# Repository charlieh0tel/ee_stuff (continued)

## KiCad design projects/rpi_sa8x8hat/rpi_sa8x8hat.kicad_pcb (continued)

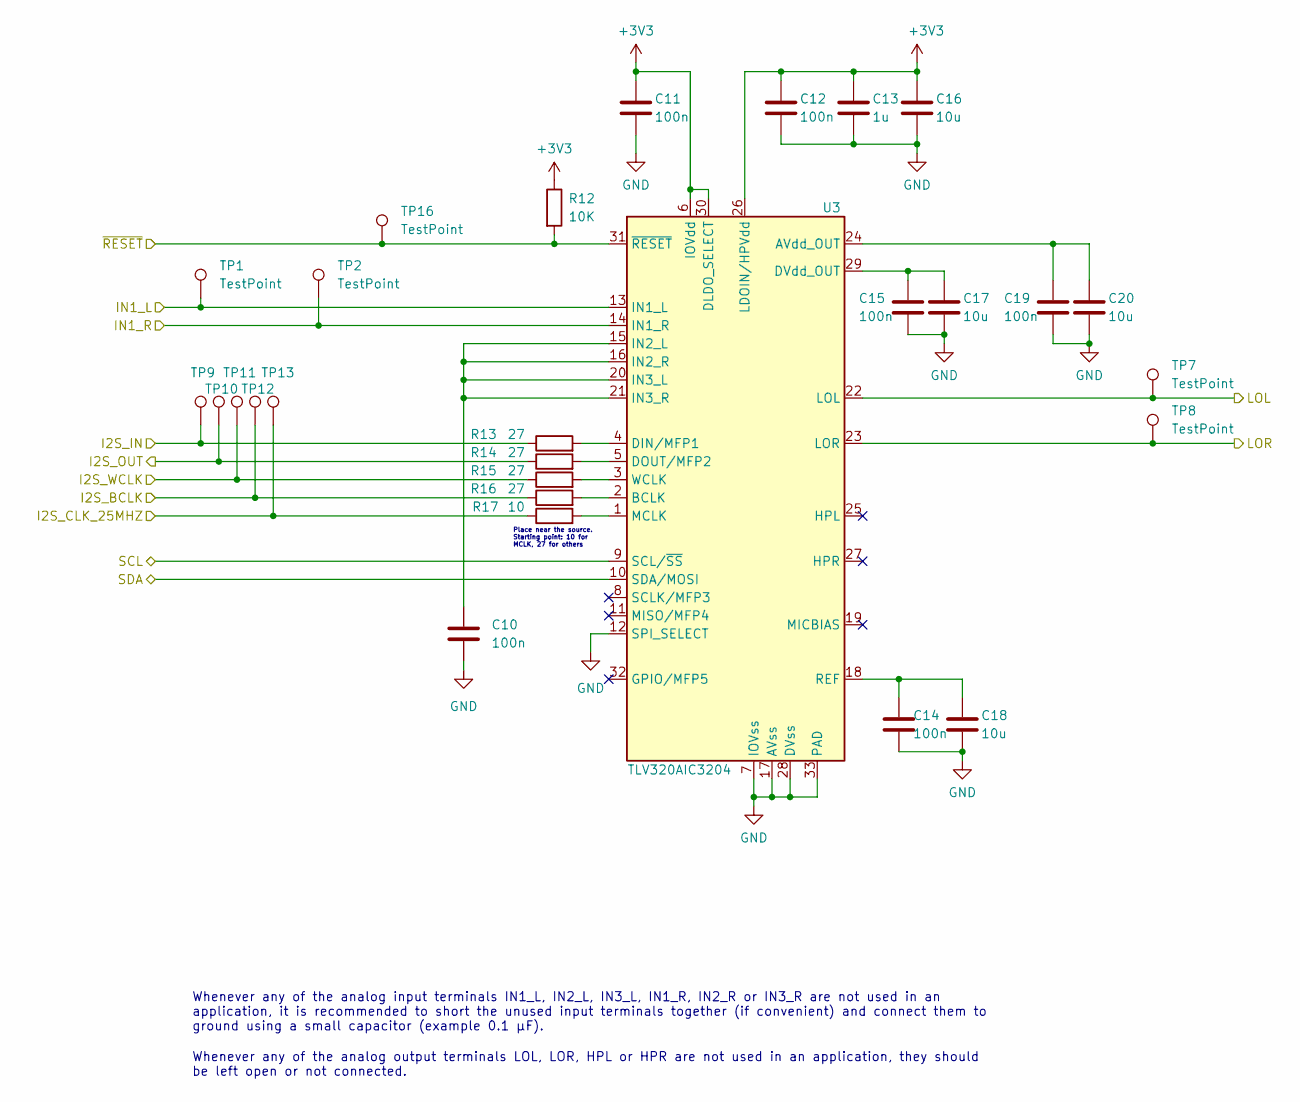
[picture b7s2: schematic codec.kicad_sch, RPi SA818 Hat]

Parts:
C10, C11, C12, C14, C15, C19: 100n; C_0402_1005Metric
C13: 1u; C_0402_1005Metric
C16, C17, C18, C20: 10u; C_0402_1005Metric
R12: 10K; R_0201_0603Metric
R13, R14, R15, R16: 27; R_0201_0603Metric
R17: 10; R_0201_0603Metric
TP1, TP2, TP7, TP8, TP9, TP10, TP11, TP12, TP13, TP16: TestPoint; TestPoint_Pad_D1.0mm
U3: TLV320AIC3204; QFN-32-1EP_5x5mm_P0.5mm_EP3.7x3.7mm

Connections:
+3V3: C11.1, C12.1, C13.1, C16.1, R12.1, U3.6 (IOVdd), U3.26 (LDOIN/HPVdd), U3.30 (DLDO_SELECT); also elsewhere on the board
/BCM_CLK_25MHZ: R17.1, TP13.1; also elsewhere on the board
/BCM_GPIO13: R12.2, TP16.1, U3.31 (~RESET); also elsewhere on the board
/BCM_I2S_BCLK: R16.1, TP12.1; also elsewhere on the board
/BCM_I2S_IN: R14.1, TP10.1; also elsewhere on the board
/BCM_I2S_OUT: R13.1, TP9.1; also elsewhere on the board
/BCM_I2S_WCLK: R15.1, TP11.1; also elsewhere on the board
/BCM_SCL: U3.9 (SCL/~SS); also elsewhere on the board
/BCM_SDA: U3.10 (SDA/MOSI); also elsewhere on the board
/Codec/IN1_L: TP1.1, U3.13 (IN1_L); also elsewhere on the board
/Codec/IN1_R: TP2.1, U3.14 (IN1_R); also elsewhere on the board
/Codec/LOL: TP7.1, U3.22 (LOL); also elsewhere on the board
/Codec/LOR: TP8.1, U3.23 (LOR); also elsewhere on the board
GND: C10.2, C11.2, C12.2, C13.2, C14.2, C15.2, C16.2, C17.2, C18.2, C19.2, C20.2, U3.7 (IOVss), U3.12 (SPI_SELECT), U3.17 (AVss), U3.28 (DVss), U3.33 (PAD); also elsewhere on the board
unnamed: C19.1, C20.1, U3.24 (AVdd_OUT)
unnamed: R16.2, U3.2 (BCLK)
unnamed: R13.2, U3.4 (DIN/MFP1)
unnamed: R14.2, U3.5 (DOUT/MFP2)
unnamed: C15.1, C17.1, U3.29 (DVdd_OUT)
unnamed: C10.1, U3.15 (IN2_L), U3.16 (IN2_R), U3.20 (IN3_L), U3.21 (IN3_R)
unnamed: R17.2, U3.1 (MCLK)
unnamed: C14.1, C18.1, U3.18 (REF)
unnamed: R15.2, U3.3 (WCLK)

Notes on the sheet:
Whenever any of the analog input terminals IN1_L, IN2_L, IN3_L, IN1_R, IN2_R or IN3_R are not used in an application, it is recommended to short the unused input terminals together (if convenient) and connect them to ground using a small capacitor (example 0.1 µF).
Place near the source. Starting point: 10 for MCLK, 27 for others
Whenever any of the analog output terminals LOL, LOR, HPL or HPR are not used in an application, they should be left open or not connected.

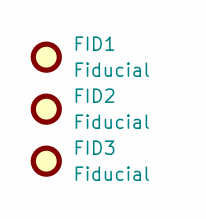
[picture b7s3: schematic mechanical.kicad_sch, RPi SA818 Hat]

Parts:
FID1, FID2, FID3: Fiducial; Fiducial_0.5mm_Mask1mm

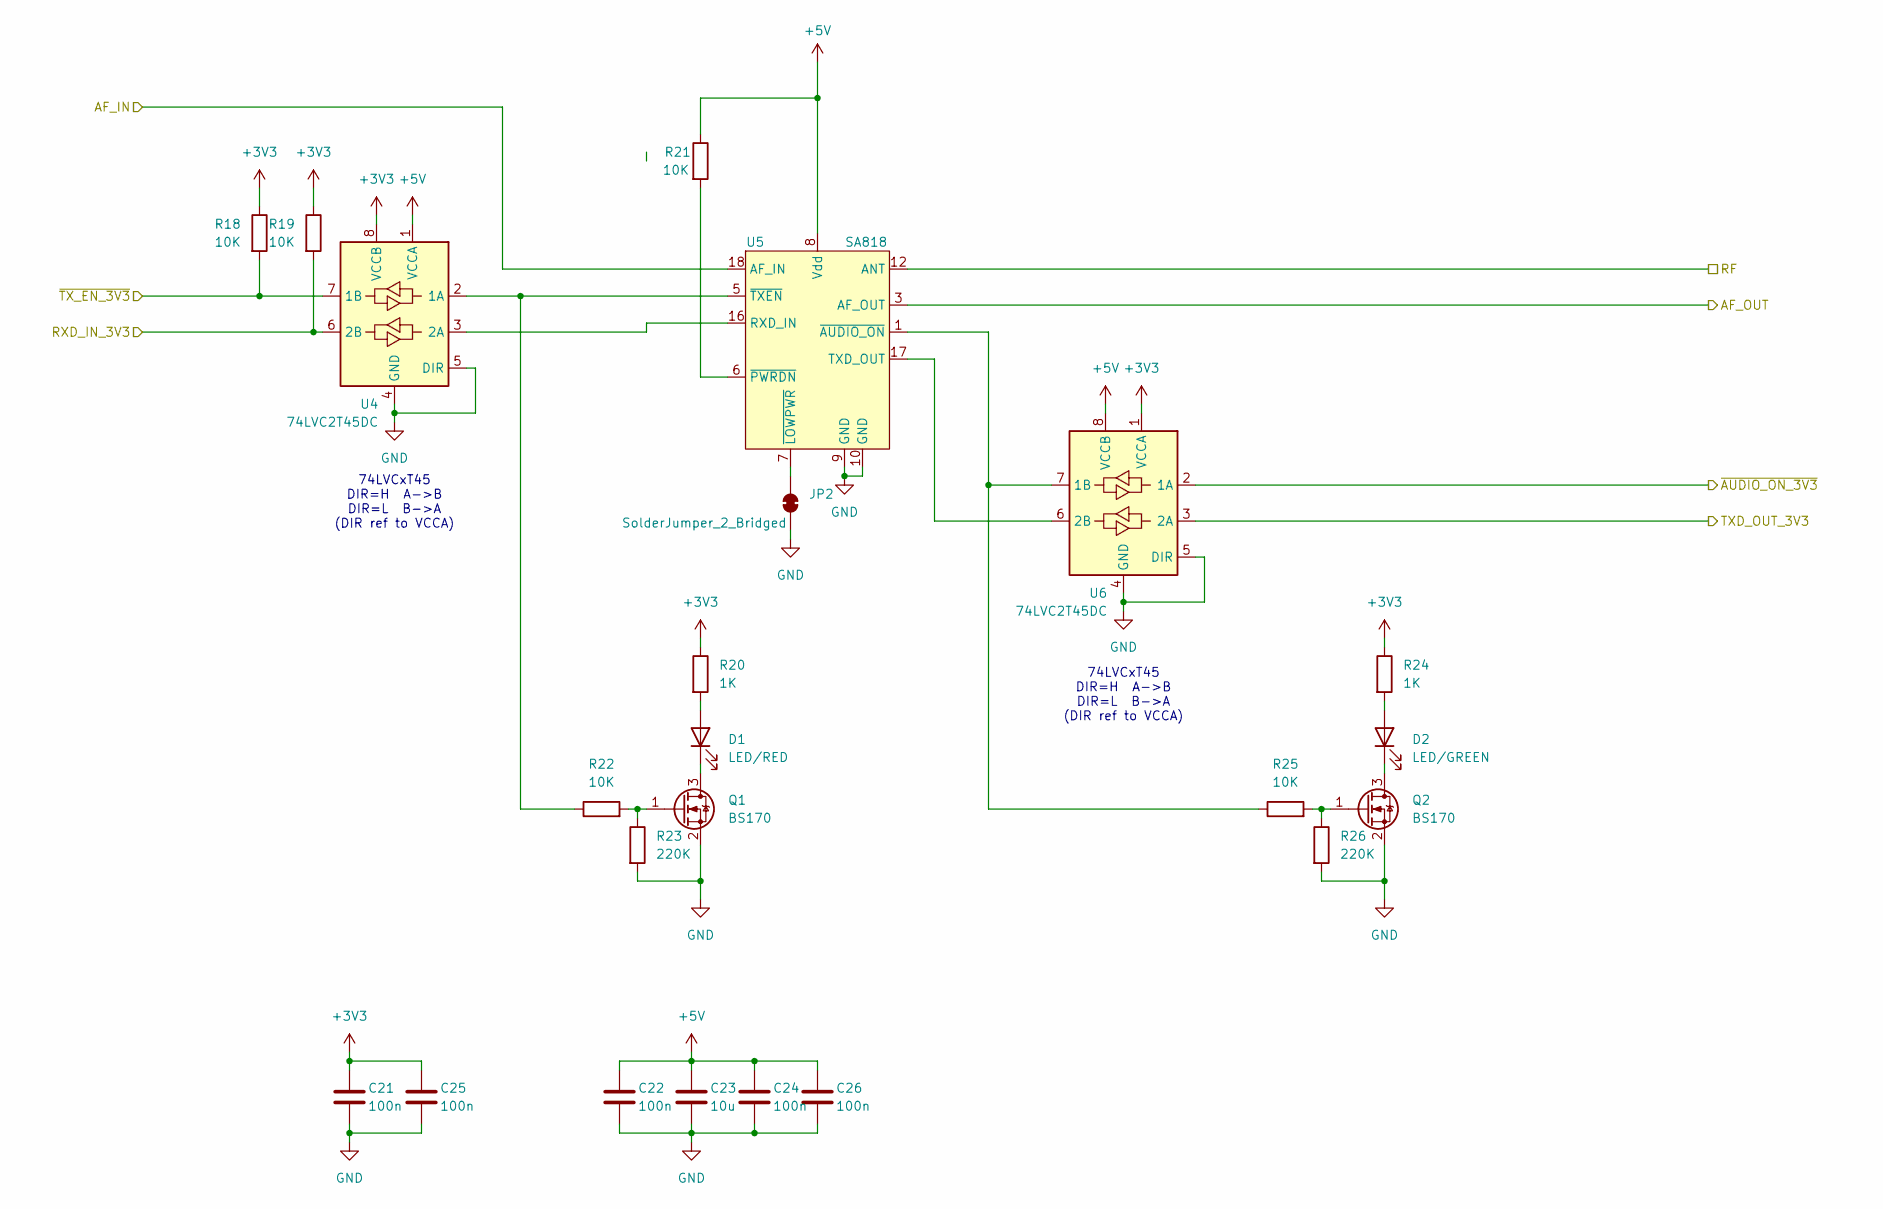
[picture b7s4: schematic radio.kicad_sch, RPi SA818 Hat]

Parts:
C21, C22, C24, C25, C26: 100n; C_0402_1005Metric
C23: 10u; C_0402_1005Metric
D1: LED/RED; LED_0603_1608Metric
D2: LED/GREEN; LED_0603_1608Metric
JP2: SolderJumper_2_Bridged; SolderJumper-2_P1.3mm_Bridged2Bar_Pad1.0x1.5mm
Q1, Q2: BS170; SOT-23
R18, R19, R21, R22, R25: 10K; R_0201_0603Metric
R20, R24: 1K; R_0402_1005Metric
R23, R26: 220K; R_0201_0603Metric
U4, U6: 74LVC2T45DC; VSSOP-8_2.3x2mm_P0.5mm
U5: SA818; SA8x8

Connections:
+3V3: C21.1, C25.1, R18.1, R19.1, R20.1, R24.1, U4.8 (VCCB), U6.1 (VCCA); also elsewhere on the board
+5V: C22.1, C23.1, C24.1, C26.1, R21.1, U4.1 (VCCA), U5.8 (Vdd), U6.8 (VCCB); also elsewhere on the board
/BCM12_GPIO: R18.2, U4.7 (1B); also elsewhere on the board
/BCM25_GPIO: U6.2 (1A); also elsewhere on the board
/BCM_RXD_IN: U6.3 (2A); also elsewhere on the board
/BCM_TXD_OUT: R19.2, U4.6 (2B); also elsewhere on the board
/L_IN: U5.3 (AF_OUT); also elsewhere on the board
/L_OUT: U5.18 (AF_IN); also elsewhere on the board
/Radio/RF: U5.12 (ANT); also elsewhere on the board
GND: C21.2, C22.2, C23.2, C24.2, C25.2, C26.2, JP2.1 (A), Q1.2 (S), Q2.2 (S), R23.2, R26.2, U4.4 (GND), U4.5 (DIR), U5.9 (GND), U5.10 (GND), U6.4 (GND), U6.5 (DIR); also elsewhere on the board
unnamed: D1.2 (A), R20.2
unnamed: D1.1 (K), Q1.3 (D)
unnamed: D2.2 (A), R24.2
unnamed: D2.1 (K), Q2.3 (D)
unnamed: JP2.2 (B), U5.7 (~LOWPWR)
unnamed: Q1.1 (G), R22.2, R23.1
unnamed: Q2.1 (G), R25.2, R26.1
unnamed: R22.1, U4.2 (1A), U5.5 (~TXEN)
unnamed: U4.3 (2A), U5.16 (RXD_IN)
unnamed: U5.17 (TXD_OUT), U6.6 (2B)
unnamed: R25.1, U5.1 (~AUDIO_ON), U6.7 (1B)
unnamed: R21.2, U5.6 (~PWRDN)

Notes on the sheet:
74LVCxT45 DIR=H A->B DIR=L B->A (DIR ref to VCCA)

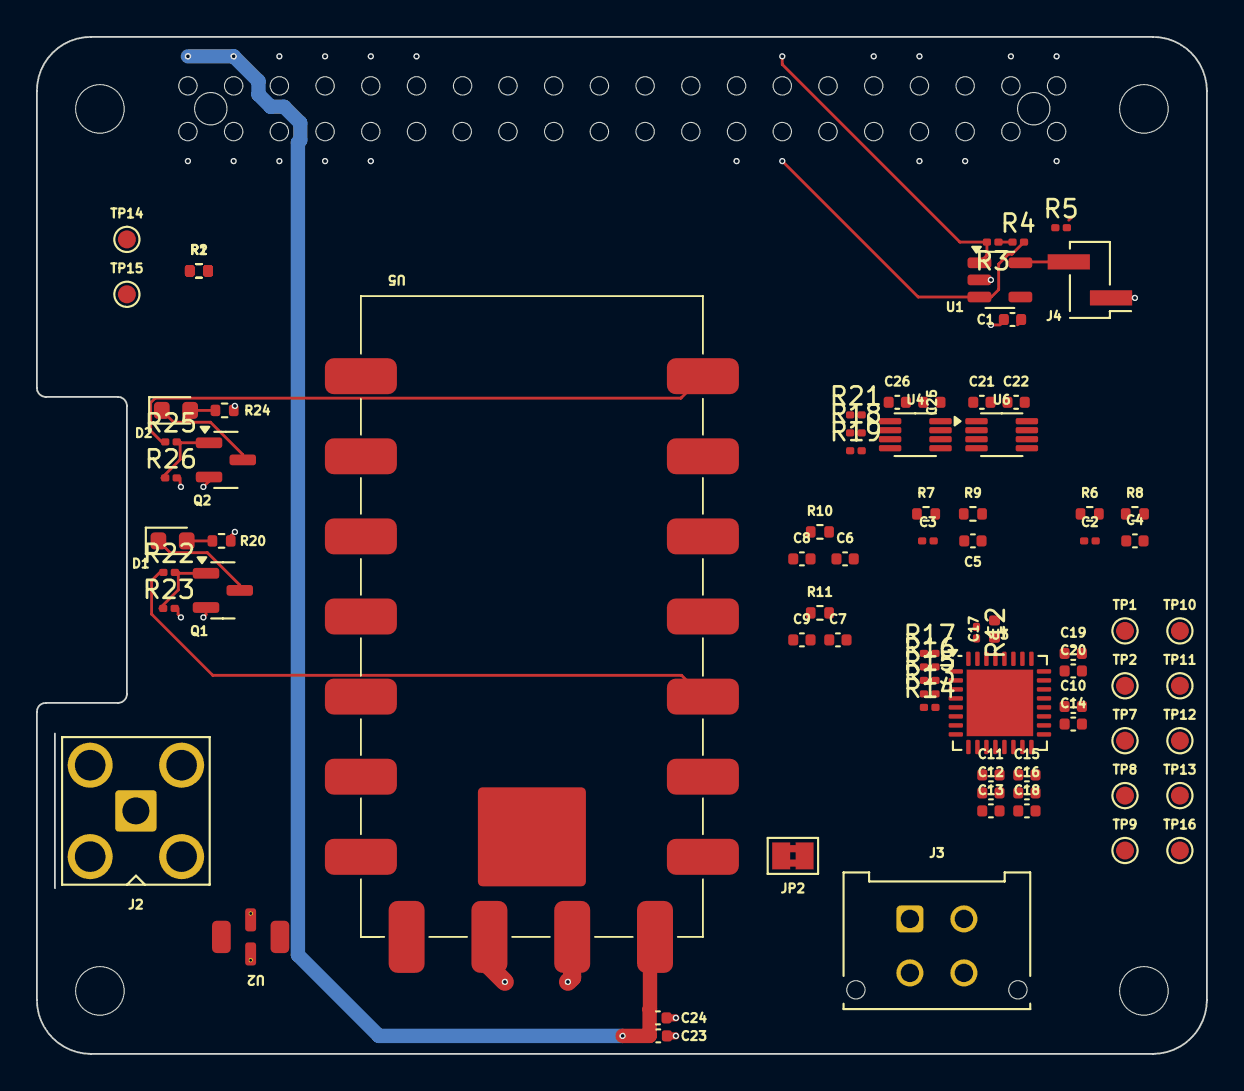
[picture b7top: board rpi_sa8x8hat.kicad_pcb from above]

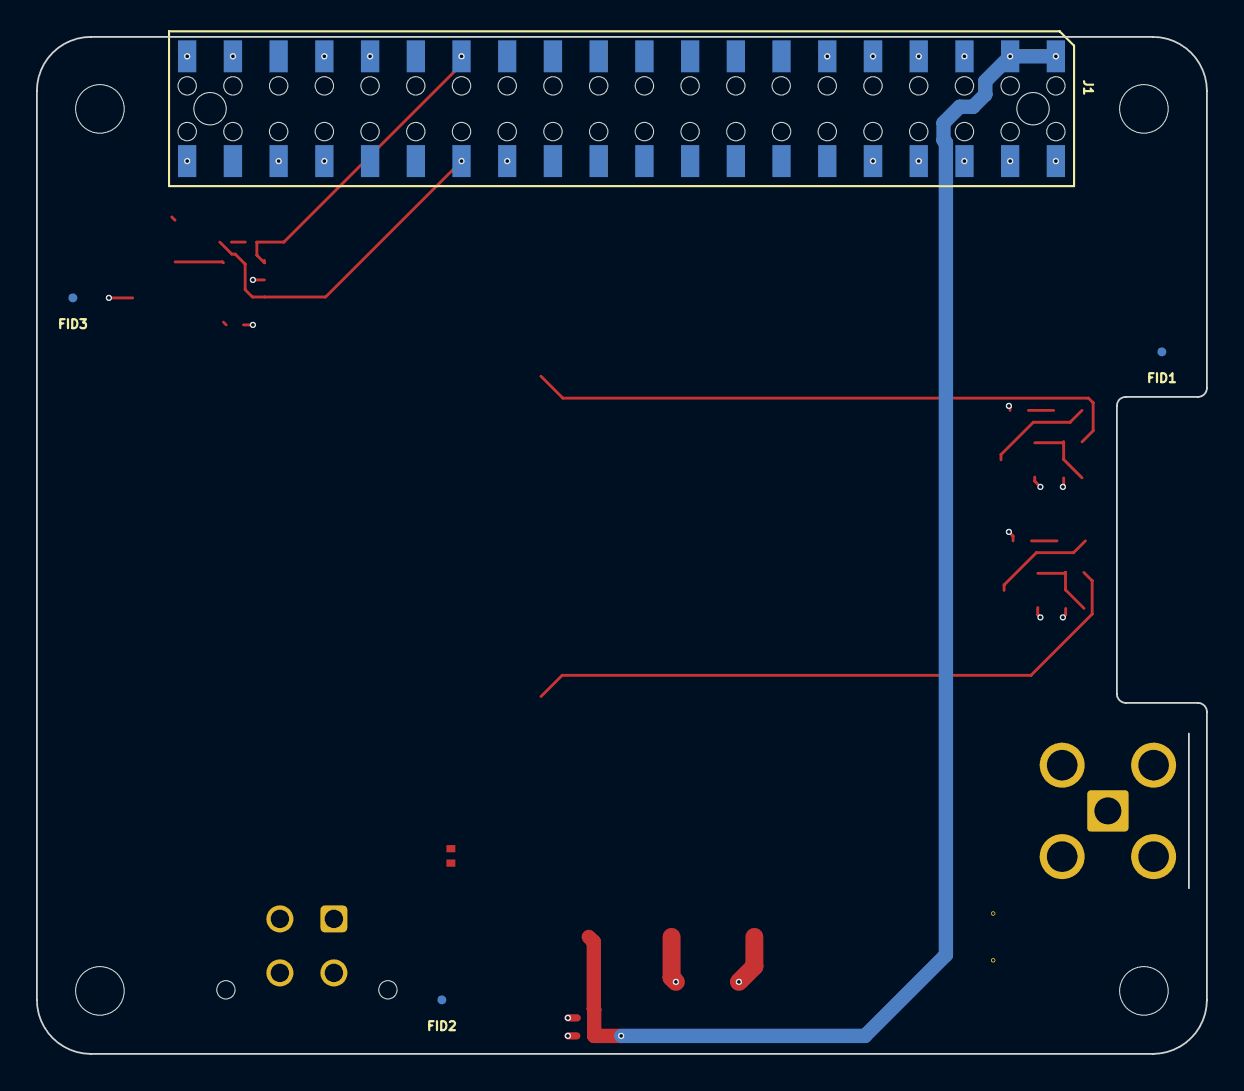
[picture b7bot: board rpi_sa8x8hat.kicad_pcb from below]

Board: 4 copper layers, 65.0 x 56.5 mm, 86 parts (4 on the bottom side), 53 nets.

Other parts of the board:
MH1, MH2, MH3, MH4: MountingHole_2.7mm_M2.5

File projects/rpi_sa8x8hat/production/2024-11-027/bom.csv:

Designator,Footprint,Quantity,Value,LCSC Part #
"C1, C10, C11, C12, C14, C15, C19, C21, C22, C24, C25, C26",0402,12,100n,
C13,0402,1,1u,
"C16, C17, C18, C20, C23",0402,5,10u,
"C2, C3",0201,2,2.2u,
"C4, C5",0402,2,33p,
"C6, C7",0402,2,4.7n,
"C8, C9",0402,2,2.2u,
D1,0603,1,LED/RED,
D2,0603,1,LED/GREEN,
"FID1, FID2, FID3",Fiducial_0.5mm_Mask1mm,3,Fiducial,
"H1, H2, H3, H4",RPi_Hat_Mounting_Hole,4,MountingHole_Pad,
J1,Samtec_HLE-120-02-XXX-DV-BE-XX-XX,1,RPi_GPIO,
J2,SMA_Amphenol_901-143_Horizontal,1,Conn_Coaxial_Small,C493445
J3,Molex_Micro-Fit_3.0_43045-0412_2x02_P3.00mm_Vertical,1,Conn_02x02_Counter_Clockwise,
JP1,SolderJumper-2_P1.3mm_Open_TrianglePad1.0x1.5mm,1,SolderJumper_2_Open,
JP2,SolderJumper-2_P1.3mm_Bridged2Bar_Pad1.0x1.5mm,1,SolderJumper_2_Bridged,
"Q1, Q2",SOT-23,2,BS170,
"R1, R12, R18, R19, R2, R21, R22, R25, R3, R4, R5",0402,11,10K,
"R10, R11, R20, R24",0402,4,1K,
"R13, R15, R16, R17",0402,4,0,
R14,0402,1,27,
"R23, R26",0402,2,220K,
"R6, R7",0402,2,100,
"R8, R9",0402,2,100K,
"TP1, TP10, TP11, TP12, TP13, TP14, TP15, TP16, TP2, TP7, TP8, TP9",TestPoint_Pad_D1.0mm,12,TestPoint,
U1,SOT-23-5,1,AT24CS32-STUM,C147891
U2,LFCN,1,LCN-160+,C879890
U3,QFN-32-1EP_5x5mm_P0.5mm_EP3.7x3.7mm,1,TLV320AIC3204, C9925
"U4, U6",VSSOP-8_2.3x2mm_P0.5mm,2,74LVC2T45DC,C15741
U5,SA8x8,1,SA818,C3001549

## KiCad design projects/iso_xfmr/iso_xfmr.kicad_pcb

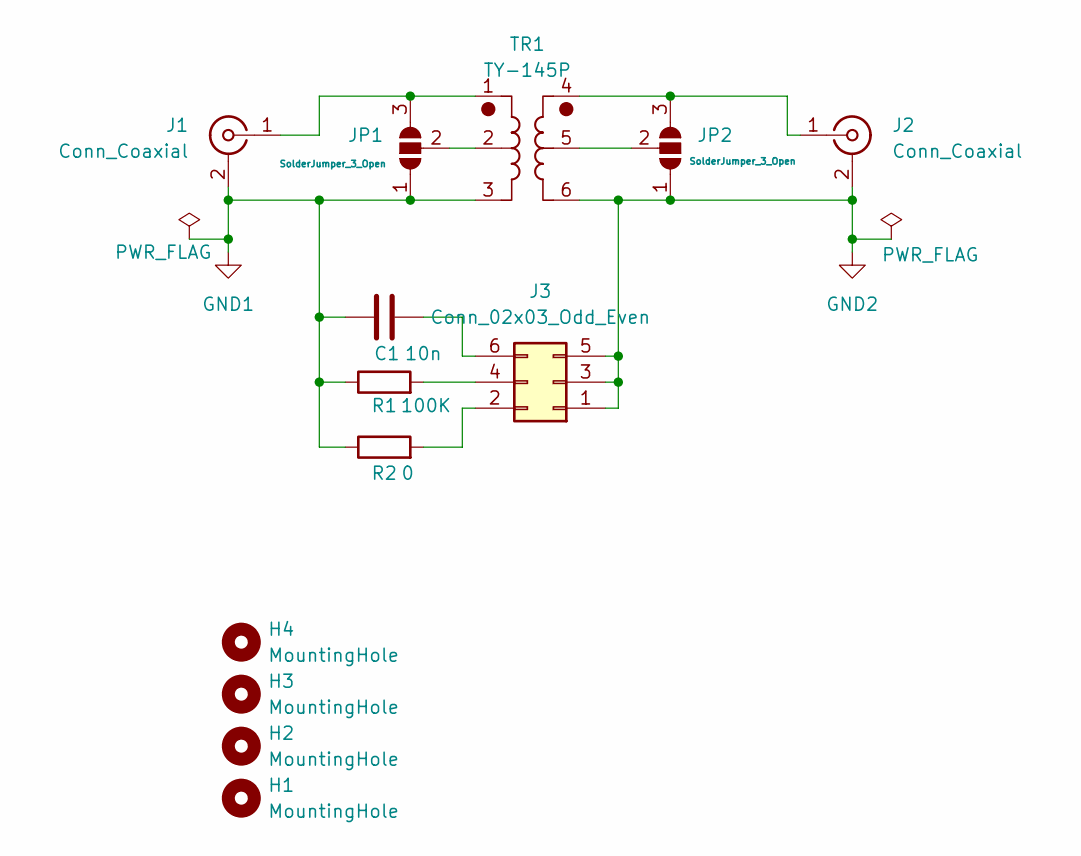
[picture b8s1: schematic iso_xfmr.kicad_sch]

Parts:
C1: 10n; C_0805_2012Metric_Pad1.18x1.45mm_HandSolder
H1, H2, H3, H4: MountingHole; MountingHole_4.3mm_M4
J1, J2: Conn_Coaxial; BNC_Amphenol_B6252HB-NPP3G-50_Horizontal
J3: Conn_02x03_Odd_Even; PinHeader_2x03_P2.54mm_Vertical
JP1, JP2: SolderJumper_3_Open; SolderJumper-3_P2.0mm_Open_TrianglePad1.0x1.5mm
R1: 100K; R_1206_3216Metric_Pad1.30x1.75mm_HandSolder
R2: 0; R_1206_3216Metric_Pad1.30x1.75mm_HandSolder
TR1: TY-145P; ty-145p

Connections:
GND1: C1.1, J1.2 (Ext), JP1.1 (A), R1.1, R2.1, TR1.3
GND2: J2.2 (Ext), J3.1, J3.3, J3.5, JP2.1 (A), TR1.6
unnamed: J1.1 (In), JP1.3 (B), TR1.1
unnamed: J2.1 (In), JP2.3 (B), TR1.4
unnamed: J3.2, R2.2
unnamed: J3.4, R1.2
unnamed: C1.2, J3.6
unnamed: JP1.2 (C), TR1.2
unnamed: JP2.2 (C), TR1.5

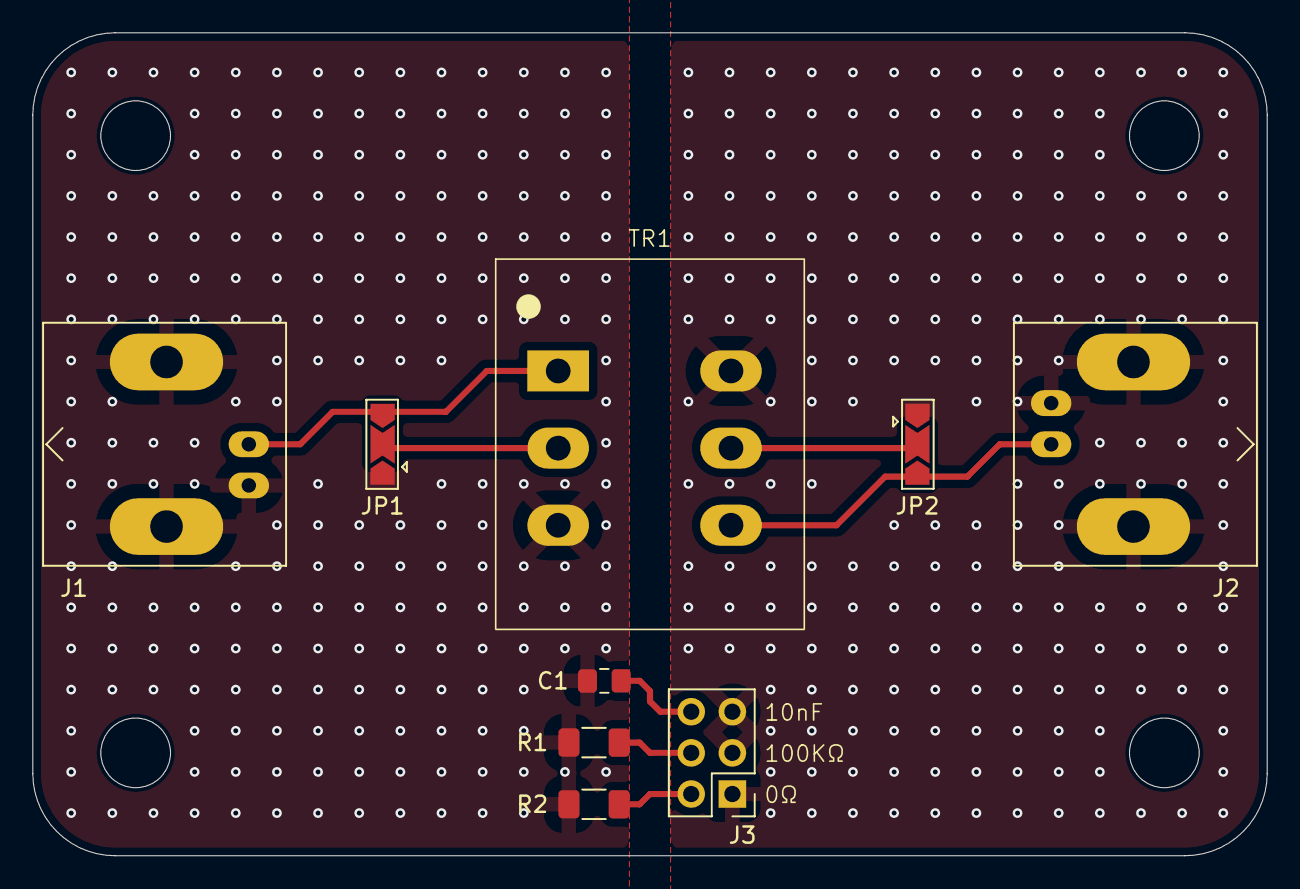
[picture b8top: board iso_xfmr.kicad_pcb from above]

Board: 2 copper layers, 76.2 x 50.8 mm, 13 parts (0 on the bottom side), 9 nets.

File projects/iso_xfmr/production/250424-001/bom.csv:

Designator,Footprint,Quantity,Value,LCSC Part #
C1,0805,1,10n,
"J1, J2",BNC_Amphenol_B6252HB-NPP3G-50_Horizontal,2,Conn_Coaxial,
J3,PinHeader_2x03_P2.54mm_Vertical,1,Conn_02x03_Odd_Even,
R1,1206,1,100K,
R2,1206,1,0,
TR1,ty-145p,1,TY-145P,

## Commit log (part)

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2024-09-17 checkpoint
2024-09-20 wip to v2
2024-09-22 v1.2
2024-09-22 prod 20240921-001
2024-09-22 fix up 0R
2024-09-22 final?
2024-09-22 part number updates
2024-09-25 rebase.
2024-09-26 prod candidate
2024-10-03 v1.2b
2024-10-03 production files for v1.2b
2024-10-25 Tweak to try to get 2d-code in the right place.
2024-10-28 Fixes LCSC for 10-pin molex microfit 3.0
2024-10-28 Minor tweaks and LCSC part numbers
2024-11-22 adds via fencing and soldermask delete on rf tracks
2024-12-05 Fix I2S series resistor values.
2024-12-17 hariwn m20 connector and uhat template
2024-12-19 first production
2025-02-04 Fixes up naming of Labjack analog inputs; no eletrical change.
2025-03-10 Clean up and push random stuff.
2025-03-18 utiltiy to do screen grab off of agilent/keysight mso \'scope
2025-03-31 Adds TODO.xt
2025-03-31 Drop the top conenctors.
2025-03-31 Fixes border outlines
2025-03-31 mo betta hats
2025-04-24 initial
2025-04-24 Small fix ups
2025-04-25 production release
2025-05-02 Regression routines.
2025-05-02 Fixes t paramers; autopep8
2025-05-11 RF Sensor Calibration
2025-05-11 autopep8 (no other changes)
2025-05-12 rf sensor cal
2025-05-12 hp 8662/3a wrapper
2025-05-13 Add zeroing and settling read per the manual.
2025-05-13 hp8663a: adds first AP does not work quirk.
2025-05-13 autopep8
2025-05-13 R&S SMB100A: add frequency check (thought it depends on the model)
2025-05-13 HP 8662A/8663A: add 8663A class and add 8662A and 8663A frequency checks
2025-05-13 Allow for set_frequency to throw ValueError.
2025-05-13 8484a: add more rf power levels to measure
2025-05-14 Latest RF sensor measurement
2025-05-14 add markdown
2025-05-14 cleanup
2025-05-14 comparison
2025-05-14 max abs err
2025-05-14 Better max abs error.
2025-05-15 Fix bad data point from R&S for 10 dBm @ 100 kHz. Refactor plotting.
    Hand-edit the csv to remove the 100 kHz @ 10 dBm measurement from the
    RS SMB100A -- it cannot do that power at that frequency. That
    explains the discrepancy.
    Move plotting out of cal_rf_sensor.py into sensor_plot.py so the plots
    can be messed with without re-taking measurements.
    Re-gen all the plots.
2025-08-15 Tool to post-process Agilent scope serial scaptures.
2025-09-20 TS-50B initial.
2025-11-12 canob - wip
2025-11-27 wayward file?
2025-12-24 Draft release version.
2025-12-25 prod
2025-12-25 Removes LCSC field from symbols for passives and LEDs (several did not match the chosen footprint)
2025-12-28 IN-18 Lead Forming Tool
2025-12-28 Was b0rken; maybe fixed?
2025-12-28 Fix IN-18 pin pattern and hole sizing
    - Correct to 14 pins in 15-position pattern (was 13 pins in 14-position)
    - Add key gap between pin 14 and pin 1 per datasheet
    - Increase hole radius to 0.7mm for FDM/PETG shrinkage compensation
    - Increase base diameter to 36mm
2025-12-28 Fixing bad rebase.
2025-12-28 Do not check in dervied STL
2025-12-28 Add IN-18 spacer for tube-to-PCB alignment
2025-12-29 Removes step file.
2026-01-01 Fixes dual diode pinning problem.
2026-01-01 Adds testpoints to make it easier to force DFU.
2026-01-01 full swd
2026-01-02 switches to tag connect TC2030
2026-01-02 Switch to SKAR-10S footprint for the rotary switch.
2026-01-02 Better silkscreen
2026-01-02 new produciton release
2026-01-31 magloop preamp
2026-02-02 magloop
2026-02-18 tighter layout
2026-02-18 Check in wayward files
2026-03-02 scrap
2026-03-07 12v smps block
2026-03-07 fix relays
2026-03-25 better design
2026-03-25 Bumped lower bandwidth up to 500 Hz
2026-03-26 minor cleanup of silkscreen; no function change
2026-03-26 change the KK from dnp to populate
2026-03-26 Fixes several calcs on the schematic
2026-04-03 Thermistor buffering.
2026-04-03 Move to where it belongs
2026-04-05 Replace instruments/ with ee-instruments submodule
2026-04-05 Add Python CI, fix lint and format issues (ruff)
2026-04-08 magloop coupler
2026-04-13 Many fixes.
2026-04-13 Open in colab link added.
2026-04-13 Thermistor notebook: verify output after rounding; fix T-dependent reporting.
    - Verify actual Vout(Tmin), Vout(Tmax) using rounded R2/R3/R4 and warn
    if either violates the requested margin. Catches a silent case where
    E12 rounding of R3 pushes both rails past the margin even though the
    reported gain looks fine.
    - Report input-filter cutoff at both temperature extremes instead of
    using ntc.r0 (25 C only), since Rsrc = Rpar(R_ntc(T), R1) varies
2026-04-13 Thermistor notebook: grid-search (R2, R3, R4) over E-series neighbors.
    Greedy independent rounding of R2, R3, R4 to the nearest E-series value
    can leave both Vout extremes outside the requested [Vout_min, Vout_max]
    margin even when a nearby combination satisfies it. Happened on the
    notebook's own default E12 parameters.
    New _find_best_R234 does a 3x3x3 grid search (R4 included because R2/R3
    ideal values scale linearly with it). Objective: feasibility first,
2026-04-13 Thermistor notebook: small cleanup pass.
    - Remove dead `p()` helper and its `import string`.
    - Drop hardcoded `ax1.set_ylim(-60, 5)` in the filter plot — was
    clipping curves that genuinely dipped below.
    - `KtoC` now `.rescale(pq.degK)`s its input, rejecting non-temperature
    quantities instead of silently stripping `.magnitude`.
    - R4 and R5 go through `eseries_wrapper` for consistency with
2026-04-13 Thermistor notebook: tidy two bits of user-facing text.
    - 'Adjust After Consideration' -> 'Adjust Only After Consideration'
    in the fixed-resistor-defaults header.
    - 'under 10K Ohm' -> 'under 10K &Omega;' in the R2/R3-too-large
    recommendation, matching the &Omega; entity used elsewhere in the
    results HTML.
2026-04-13 Thermistor notebook: render resistor values as kΩ / Ω in results table.
    Previously the NTC R₀ and the selected R1-R5 values were interpolated
    as bare pq.Quantity, which uses the quantities library's default
    format and produces strings like '2700.0 ohm'. Add an fmt_r helper
    that rescales to ohms, switches to kΩ above 1 kΩ, and uses the
    &Omega; HTML entity to match the rest of the results table.
2026-04-13 Thermistor notebook: clear stale cell outputs and execution counts.
    Keeps the file small and avoids checking in pre-rendered results that
    won't match a fresh run after the recent solver changes.
2026-04-13 Thermistor notebook: add ADC resolution and 2-point linearity analysis.
    Answers the actual figure of merit for a temperature chain: 'how many
    m°C per ADC LSB, and how much does a naive 2-point calibration err?'
    - New `adc_bits` @param input (default 12-bit). Assumes ratiometric
    ADC with Vref = Vdd.
    - `analyze_resolution` computes dV_out/dT analytically from the Beta
    model and reports °C/LSB at Tmin/Tmax plus best/worst over the range,
2026-04-13 Thermistor notebook: drop 2-point linear-fit metric from resolution section.
    Calibration in the target application is LUT-based, so the raw T(code)
    nonlinearity is absorbed in the LUT and the 2-point-linear-fit residual
    is not a meaningful error metric. Remove the nonlinearity_max_mK field,
    the residual_K array, the bottom plot subplot, and the corresponding
    HTML row. Keep °C/LSB — that's the intrinsic ADC-quantization-limited
    resolution and is independent of calibration method.
2026-04-13 Thermistor notebook: auto-run Colab + minor label tweaks.
    - Colab badge URL gets ?autorun=true so clicking it lands on a
    fully-rendered notebook with tables and plots already populated.
    - Drop 'Don't Touch or ' from the fixed-resistor-defaults header;
    'Adjust Only After Consideration' is enough.
    - Resolution plot y-label 'm°C / LSB' reads cleaner than the previous
    '°C / LSB (m°C)', which mixed the quantity and its unit awkwardly.
2026-04-13 Thermistor notebook: satisfy ruff check and ruff format.
    - analyze_resolution: drop V_in / V_out / offset / R3 / R4 locals.
    They were leftovers from the 2-point-linear-fit code that was
    removed in commit aa3ad64; the analytical derivative path doesn't
    reference them. Fixes ruff F841.
    - Apply ruff format: 2-space -> 4-space indentation throughout and
    line-length normalization. Output of the calculator is unchanged
2026-04-13 Thermistor notebook: drop ?autorun=true, add Run-All instruction.
    ?autorun=true isn't actually a Colab URL parameter — confirmed by
    observation. Users opening the notebook from GitHub need to run cell 3
    (definitions) at least once before the run:auto params cell can work,
    so the realistic UX is 'Run all once, then tweak interactively.'
    Replace the fake URL flag with a short note under the Colab badge
    directing first-time users to Runtime -> Run all.
2026-04-13 Thermistor notebook: clarify Run-All banner for Colab playground mode.
    Colab's form run:auto is disabled in playground mode, which is what
    you get when a notebook is opened directly from GitHub. Add a
    Shift+Enter manual-refresh instruction and a note that auto-update
    only kicks in after saving a copy to Drive.
2026-04-13 Clean up instructions
2026-04-13 Clean up instructions.
2026-04-13 Improve instructions.
2026-05-17 Diode small signal derivation
2026-05-17 Add GitHub Actions workflow to build LaTeX PDF and deploy to GitHub Pages
2026-05-17 add practical example table
2026-05-17 Add regime figure and temperature-dependence section to diode small-signal note
    - make_figure.py generates regimes_figure.pdf (I-V curve + regime ruler)
    - Makefile wires figure generation as a prerequisite for the PDF build
    - CI workflow runs make_figure.py before the LaTeX action
    - tex: include figure, expand temperature-dependence into its own subsection
2026-05-17 more tex-y labels
2026-05-17 * bug fixes * clean up * junction capacitance * summary
2026-05-17 Fixed some bugs.
2026-05-17 Fix figure script name and install matplotlib in CI
2026-05-17 More bug fixes
2026-05-17 Fix figure script name in CI (make_regimes_figure.py)
2026-05-17 Install texlive in CI for usetex figure rendering
2026-05-17 bunch of bug fixes
2026-05-17 Add texlive-latex-recommended for type1cm.sty
2026-05-17 Add texlive-latex-extra for type1cm.sty
2026-05-17 Switch to texlive-full and run pdflatex directly via make
2026-05-17 More bug fixes; better layout
2026-05-17 many fixes
2026-05-17 more fixes; cleanup
2026-05-18 some fixes
2026-05-18 Split reactive small-signal section into diode_reactive.tex
    Build, Makefile, and Pages workflow now produce and publish both
    diode_smallsignal.pdf and diode_reactive.pdf.
2026-05-22 Add CC BY-NC-SA 4.0 license
2026-05-22 Move license notice to \thanks footnote on author line
2026-05-22 Define Shockley equation terms immediately after eq 1
2026-05-22 Move ideality factor note to regime boundaries section
2026-05-22 Editorial fixes: punctuation, forward refs, split detector/mixer description
2026-05-22 Editorial pass: clarity, redundancy, and phrasing fixes
2026-05-23 Add planning notes for short-form square-law explainer
2026-05-23 Add newsletter article draft: A Diode Is Not a Square-Law Device
2026-05-23 Add newsletter figure variant; refactor figure script with --newsletter flag
2026-05-23 Add brief note on high-level switching mixers
2026-05-23 Add Further Reading section with link to companion technical note
2026-05-23 Update .gitignore for LaTeX artifacts and PDFs; ruff format figure script
2026-05-23 Fix further reading URL to link directly to companion PDF
2026-05-23 Update planning notes to reflect current draft state
2026-05-23 Add QEX submission notes and format requirements to planning doc
2026-05-23 Add QEX article plan to planning notes
2026-05-23 Add QEX article draft and local build target
2026-05-23 Fix overfull hbox in Table 2 header
2026-05-23 Editorial pass on QEX draft: fix citations, consistency, prose
2026-05-30 remove
